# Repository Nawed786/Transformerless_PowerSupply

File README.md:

# Transformerless Power Supply Project

This is a sample project of Powerless Transformer system by Nawed Ahmad.

🛠️ Project Description
A compact and low-cost AC to DC power supply without using bulky transformers. Ideal for small electronics and IoT devices.

📦 Features
 - Capacitor-based step-down design

 - Full-wave rectification

 - Voltage regulation

 - Compact and efficient

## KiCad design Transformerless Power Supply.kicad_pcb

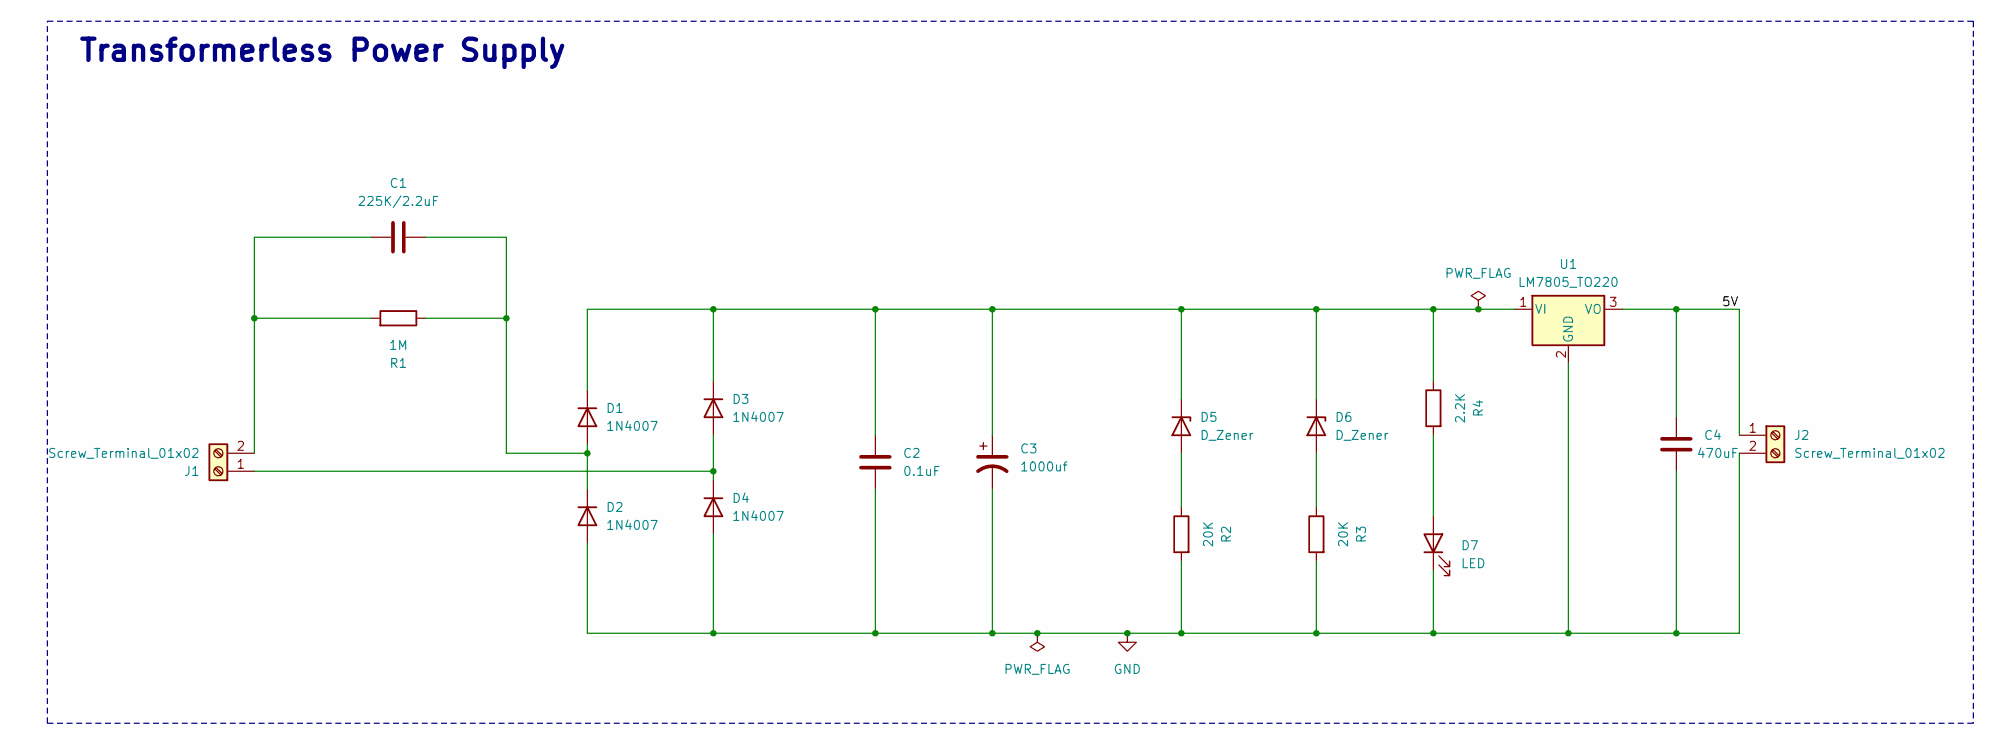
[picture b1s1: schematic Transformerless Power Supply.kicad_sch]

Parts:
C1: 225K/2.2uF; C_Disc_D4.7mm_W2.5mm_P5.00mm
C2: 0.1uF; CP_Radial_D10.0mm_P5.00mm
C3: 1000uf; CP_Radial_D10.0mm_P3.80mm
C4: 470uF; C_Rect_L18.0mm_W6.0mm_P15.00mm_FKS3_FKP3
D1, D2, D3, D4: 1N4007; D_DO-41_SOD81_P10.16mm_Horizontal
D5, D6: D_Zener; D_A-405_P7.62mm_Horizontal
D7: LED; LED_D5.0mm
J1, J2: Screw_Terminal_01x02; TerminalBlock_bornier-2_P5.08mm
R1: 1M; R_Axial_DIN0207_L6.3mm_D2.5mm_P7.62mm_Horizontal
R2, R3: 20K; R_Axial_DIN0207_L6.3mm_D2.5mm_P7.62mm_Horizontal
R4: 2.2K; R_Axial_DIN0207_L6.3mm_D2.5mm_P7.62mm_Horizontal
U1: LM7805_TO220; TO-220-3_Vertical

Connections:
/5V: C4.1, J2.1, U1.3 (VO)
GND: C2.2, C3.2, C4.2, D2.2 (A), D4.2 (A), D7.1 (K), J2.2, R2.2, R3.2, U1.2 (GND)
unnamed: C1.2, D1.2 (A), D2.1 (K), R1.1
unnamed: C2.1, C3.1, D1.1 (K), D3.1 (K), D5.1 (K), D6.1 (K), R4.1, U1.1 (VI)
unnamed: D3.2 (A), D4.1 (K), J1.1
unnamed: D5.2 (A), R2.1
unnamed: D6.2 (A), R3.1
unnamed: D7.2 (A), R4.2
unnamed: C1.1, J1.2, R1.2

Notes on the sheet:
Transformerless Power Supply

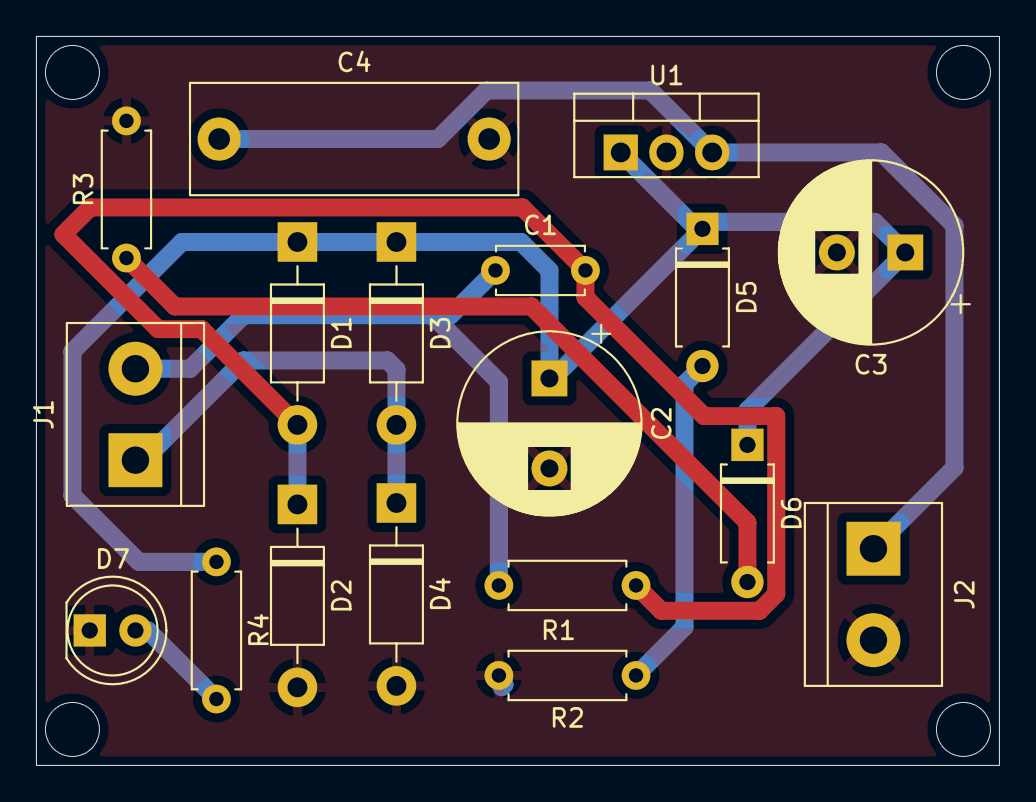
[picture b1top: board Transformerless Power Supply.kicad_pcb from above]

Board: 2 copper layers, 53.5 x 40.5 mm, 18 parts (0 on the bottom side), 9 nets.

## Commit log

2025-05-29 first commi
2025-05-29 Add:image of pcb
2025-05-29 Update: Readme Content
